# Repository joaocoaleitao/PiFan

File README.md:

# PiFan
A simple opensource project of an hat to cool you Raspberry.

Started this project because mostly all my Raspberrys end up overheating and then throttling.
So here it is!
The PiFan!
Simply put is a stackable HAT for raspberry, it can run a 100% all the time if you remove the jumper JP3 and that way you can also use the GPIO 17 for other things. Or you can keep the jumper and run the script in Python at boot and it will use the settings to control the speed through PWM.

My first tests suggest a maximum temperature of around 50C when using the fan while testing with "cpuburn-a53".

The HAT can slide down the existing GPIO pins and be tightened with a screw or you can solder a female connector (which can be the long pin version so you can stack another hat on top.)

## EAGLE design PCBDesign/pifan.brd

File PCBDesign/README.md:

# PiFan
The files in this directory are the EagleCad project as well as the Gerber files generated for production.

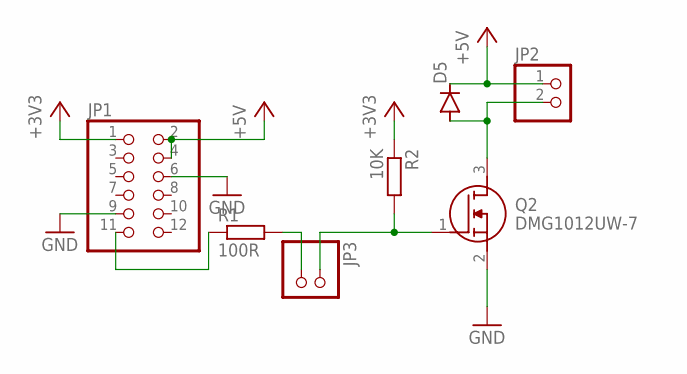
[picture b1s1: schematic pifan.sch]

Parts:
D5: DIODE-SOD123; SOD123
JP1: PINHD-2X6; 2X06
JP2: PINHD-1X2; 1X02
JP3: PINHD-1X21X02SQUARE; 1X02SQUARE
Q2: DMG1012UW-7; SOT65P210X100-3N
R1: 100R; R0805
R2: 10K; R0805

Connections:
+3V3: JP1.1, R2.1
+5V: D5.C, JP1.2, JP1.4, JP2.1
GND: JP1.6, JP1.9, Q2.2 (S)
unnamed: JP1.11, R1.1
unnamed: JP3.2, R1.2
unnamed: D5.A, JP2.2, Q2.3 (D)
unnamed: JP3.1, Q2.1 (G), R2.2

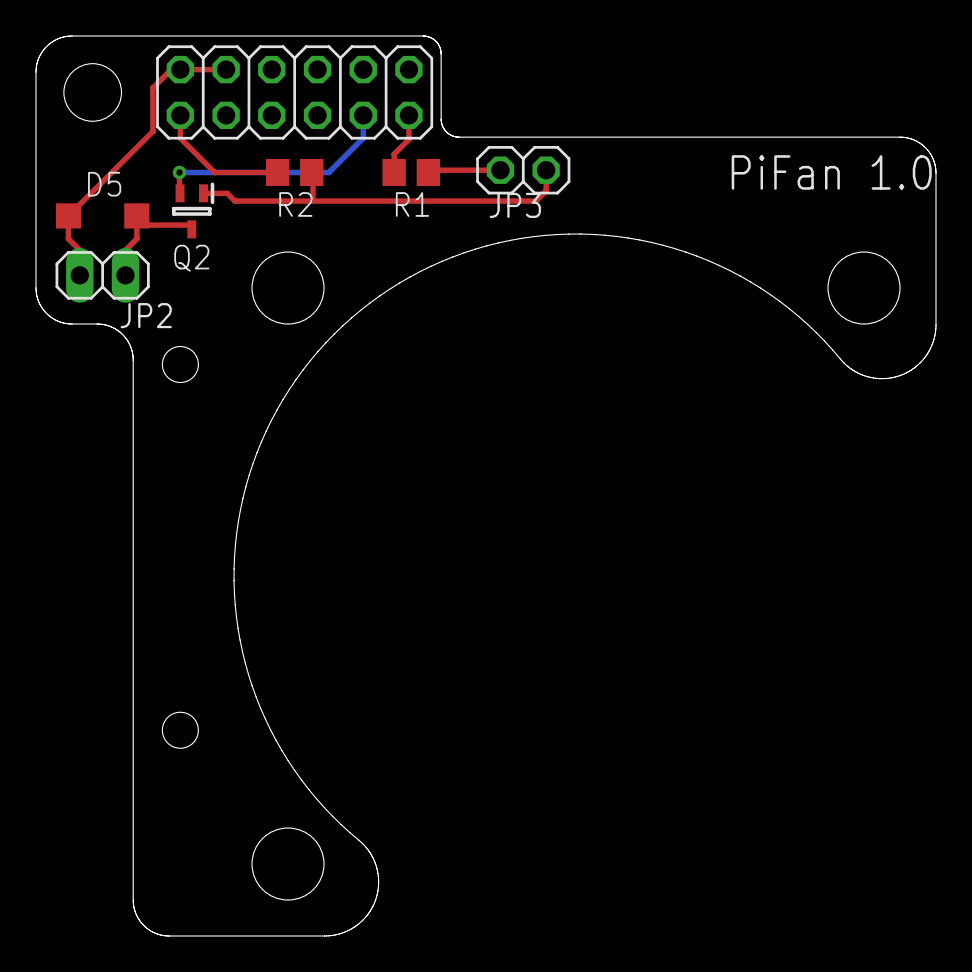
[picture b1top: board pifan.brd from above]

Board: 2 copper layers, 50.0 x 50.0 mm, 7 parts (0 on the bottom side), 7 nets.

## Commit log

2022-02-04 Python Script first version.
2022-02-05 Latest code on python script.
2022-02-05 PCB designs and gerber files if you just want to send to production.
2022-02-05 Readme update
